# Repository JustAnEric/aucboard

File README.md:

# Aucboard

Revision 2 Aucboard

> [!NOTE]
> This is my first ever hardware project involving CAD/PCB design, if there are any issues you can create one: [Create an issue](https://github.com/JustAnEric/aucboard/issues/new)

Aucboard in its design aims to provide **high fidelity**, 384KHz audio to listeners in a small package.

The hardware I am using/have used to make this project possible:

| Link | Supplier/Seller | Approx. Price |
|------|-----------------|---------------|
| [Common PCM5102A DAC breakout board](https://www.amazon.com.au/VGOL-GY-PCM5102-Compatible-Ardu-inos-Raspberry/dp/B0F631QSCH) | Amazon AU | ~A$20.39 |
| [Raspberry Pi(R) Zero 2 W](https://www.raspberrypi.com/products/raspberry-pi-zero-2-w) | Hack Club (find options near you) | ~US$15.00 |
| [SSD1306 Monochrome OLED display](https://www.amazon.com.au/s?k=ssd1306) | Find options near you | ~A$15.00 - ~A$25.00 |
| Total | | A$69.89 - A$79.89 |

> [!IMPORTANT]
> ***For the perspective of Hack Club's Half Life, I have already bought the Common PCM5102A DAC breakout board, Raspberry Pi(R) Zero 2 W and the SSD1306 Monochrome OLED display myself. PCB manufacturing and fabrication costs are going to be receiving the most funding for this project.***

Tools used:

* KiCAD

The optimal fabrication solution I figured was JLCPCB, as PCBWay can charge $5-10 more per board. If you end up building this yourself, make sure to factor in those costs and whether you'd like PCBA, or manual work. For me, I'll be using PCBA.

## Board revisions

This section will go into the design process of the board.

### Rev 1

The very simplistic schematic of the board is shown below, as it was in V1 (forgetting DAC2, GPIO27, GPIO22, GPIO17, GPIO23 and AGND, I was setting up layouts for an amplifier)

* RPIZ2W1 is the header for the Raspberry Pi Zero 2 W's GPIO connections,
* GPIO5, GPIO6, GPIO13 and GPIO26 are connected to SW1-SW4,
* DISP1 is the SSD1306 OLED display module,
* DAC1 is the 6 pins the DAC provides for outputting a basic line-level signal from its preinstalled AUX jack

And a bit of placement magic onto the PCB, including a ground plane with a 0.2 mm clearance, 0.3 mm thermal relief gap and solid pad connections for some shielding:

(The text and barcode was on the F.Cu layer, I didn't know this at the time and I fixed it to F.Silkscreen instead...)

So afterwards, the PCB would look like this:

<div>

</div>

I tried my best to keep the DIN cable routed at the back and short, I wanted minimal crosstalk between the power and signal lines as is typical practice when making boards like this. Constraints required me to use a lot of vias as you can see via the dots on traces (as shown in KiCAD).

#### Flaws with this current design

This PCB has no real amplification to it. So, the line-level signal coming out from the DAC would actually fail to drive basic headphones properly unfortunately. Another design is needed, and note to self for next time:
* I should fill up as much board space as I can,
* Maybe put the amplifier next to the display,
* Optimize my traces a little more by shortening them and planning out better paths, for the amplifier this is especially important....

### Rev 2

In Revision 2.0, I added an amplifier called the MAX97220AETE+T into the mix and moved some things around. I made the buttons surface-mount so it would be way easier for me to route traces properly across the board. Additionally, there are now less vias, making the board way cleaner. This was done over 10 hours of work approximately, most of me was trying to understand the optimal circuit the PDF datasheet recommended. The amp circuit is effectively the same, but I replaced the input smoothing 0.47uF capacitors with 1uF capacitors to allow a decrease in frequency to ~15Hz rather than ~33Hz minimum.

On the PCB, it received a full re-design, including with how components are placed. Now the DAC is flipped around to the other side and rotated, giving easier access for the amplifier circuit to work properly. There are now two (bigger) ground planes stitched to each other instead of just the one, aiming to provide better thermal spreading, better EMI shielding meaning better signal integrity, and lower impedence ground return paths.

The routing spaghetti is definitely less, automatically allowing for greater reliability because not everything is very packed like Revision 1.

## Software journaling

The software implemented right now at [firmware/](firmware/) is very basic, and definitely needs greater development. Though, the greatest achievement I'm proud of is how `miniaudio` plays audio so smoothly on constrained devices. Furthermore, I can edit the audio stream *in software* rather than constantly configuring a tool like `pactl` filters.

In the first few commits, `pygame` was implemented due to its simpler `pygame.mixer`, but if I kept it like that, audio quality would've been sacrificed heavily for its simplicity. **Heavy stuttering and jitter** would have occurred for the tests directly because of Python (as the same happens with PyAudio too). Miniaudio simplifies it *way* down for Aucboard.

## Disclaimers!

This is an **ongoing project**, and I have not at all started with software yet. This README right now only shows a basic design, where everything may not be up to date as I revise.

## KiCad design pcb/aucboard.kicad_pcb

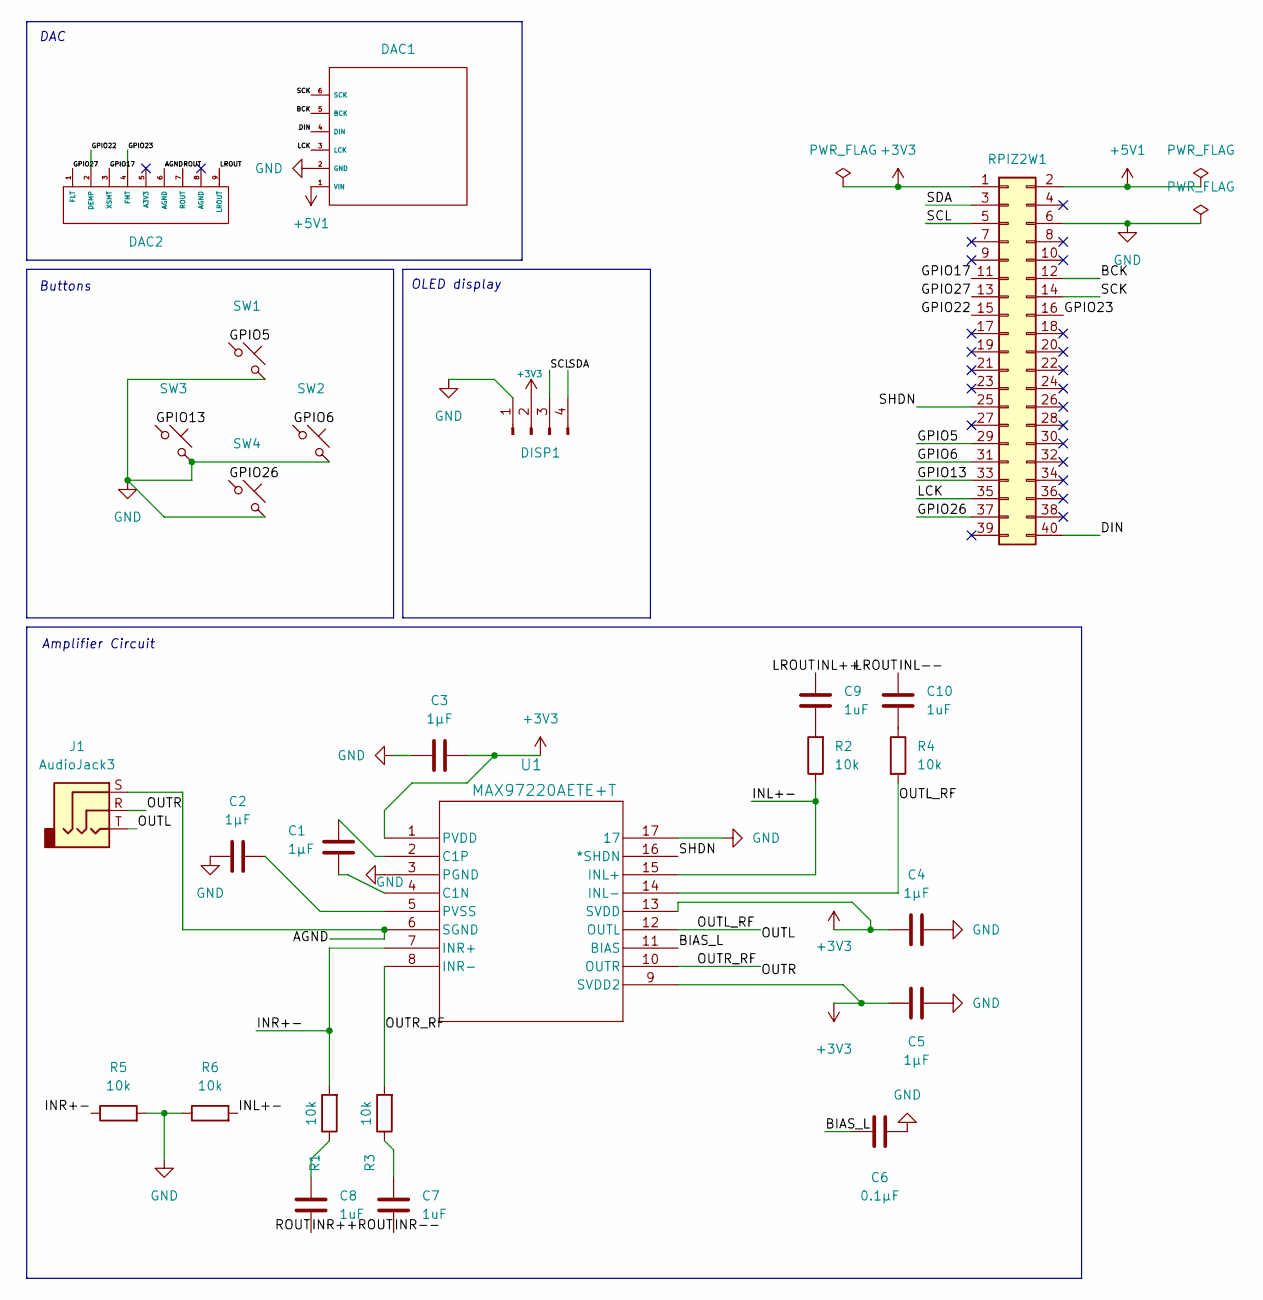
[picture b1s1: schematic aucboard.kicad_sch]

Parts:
C1, C2, C3, C4, C5: 1µF; C_0805_2012Metric_Pad1.18x1.45mm_HandSolder
C6: 0.1µF; C_0805_2012Metric_Pad1.18x1.45mm_HandSolder
C7, C8, C9, C10: 1uF; C_0805_2012Metric_Pad1.18x1.45mm_HandSolder
DAC1: PinSocket_1x06_P2.54mm_Vertical
DAC2: PinSocket_1x09_P2.54mm_Vertical
DISP1: Conn_01x04_Pin; PinSocket_1x04_P2.54mm_Vertical
J1: AudioJack3; Jack_3.5mm_CUI_SJ1-3513N_Horizontal
R1, R2, R3, R4, R5, R6: 10k; R_0805_2012Metric_Pad1.20x1.40mm_HandSolder
RPIZ2W1: Conn_02x20_Odd_Even; PinSocket_2x20_P2.54mm_Vertical
SW1, SW2, SW3, SW4: SW_Push; SW_SPST_PTS645Sx43SMTR92
U1: MAX97220AETE+T; 21-0136I_T1633-4_MXM

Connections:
+3V3: C3.2, C4.1, C5.2, DISP1.2, RPIZ2W1.1, U1.1 (PVDD), U1.9 (SVDD2), U1.13 (SVDD)
+5V1: DAC1.1 (VIN), RPIZ2W1.2
/AGND: DAC2.6 (AGND), J1.S, U1.6 (SGND)
/BCK: DAC1.5 (BCK), RPIZ2W1.12
/BIAS_L: C6.1, U1.11 (BIAS)
/DIN: DAC1.4 (DIN), RPIZ2W1.40
/GPIO5: RPIZ2W1.29, SW1.1
/GPIO6: RPIZ2W1.31, SW2.1
/GPIO13: RPIZ2W1.33, SW3.1
/GPIO17: DAC2.3 (XSMT), RPIZ2W1.11
/GPIO22: DAC2.2 (DEMP), RPIZ2W1.15
/GPIO23: DAC2.4 (FMT), RPIZ2W1.16
/GPIO26: RPIZ2W1.37, SW4.1
/GPIO27: DAC2.1 (FLT), RPIZ2W1.13
/INL++: C9.1, C10.1, DAC2.9 (LROUT)
/INL+-: R2.1, R6.2, U1.15 (INL+)
/INR++: C7.2, C8.2, DAC2.7 (ROUT)
/INR+-: R1.2, R5.1, U1.7 (INR+)
/LCK: DAC1.3 (LCK), RPIZ2W1.35
/OUTL: J1.T, R4.2, U1.12 (OUTL), U1.14 (INL-)
/OUTR: J1.R, R3.2, U1.8 (INR-), U1.10 (OUTR)
/SCK: DAC1.6 (SCK), RPIZ2W1.14
/SCL: DISP1.3, RPIZ2W1.5
/SDA: DISP1.4, RPIZ2W1.3
GND: C2.1, C3.1, C4.2, C5.1, C6.2, DAC1.2 (GND), DISP1.1, R5.2, R6.1, RPIZ2W1.6, SW1.2, SW2.2, SW3.2, SW4.2, U1.3 (PGND), U1.17
unnamed: C7.1, R3.1
unnamed: C8.1, R1.1
unnamed: C9.2, R2.2
unnamed: C10.2, R4.1
unnamed: C1.2, U1.4 (C1N)
unnamed: C1.1, U1.2 (C1P)
unnamed: C2.2, U1.5 (PVSS)

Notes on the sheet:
Amplifier Circuit
DAC
OLED display
Buttons

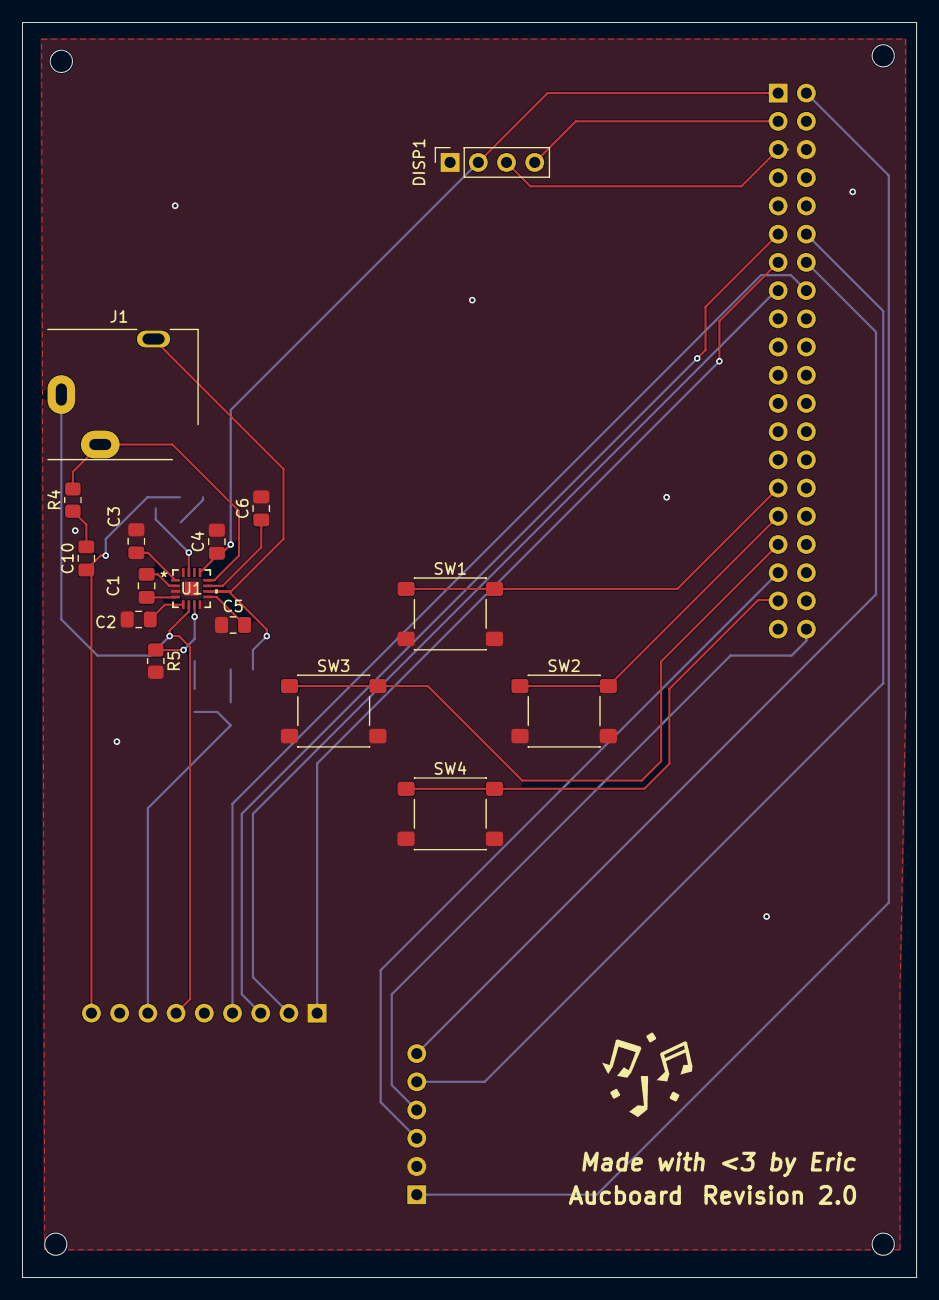
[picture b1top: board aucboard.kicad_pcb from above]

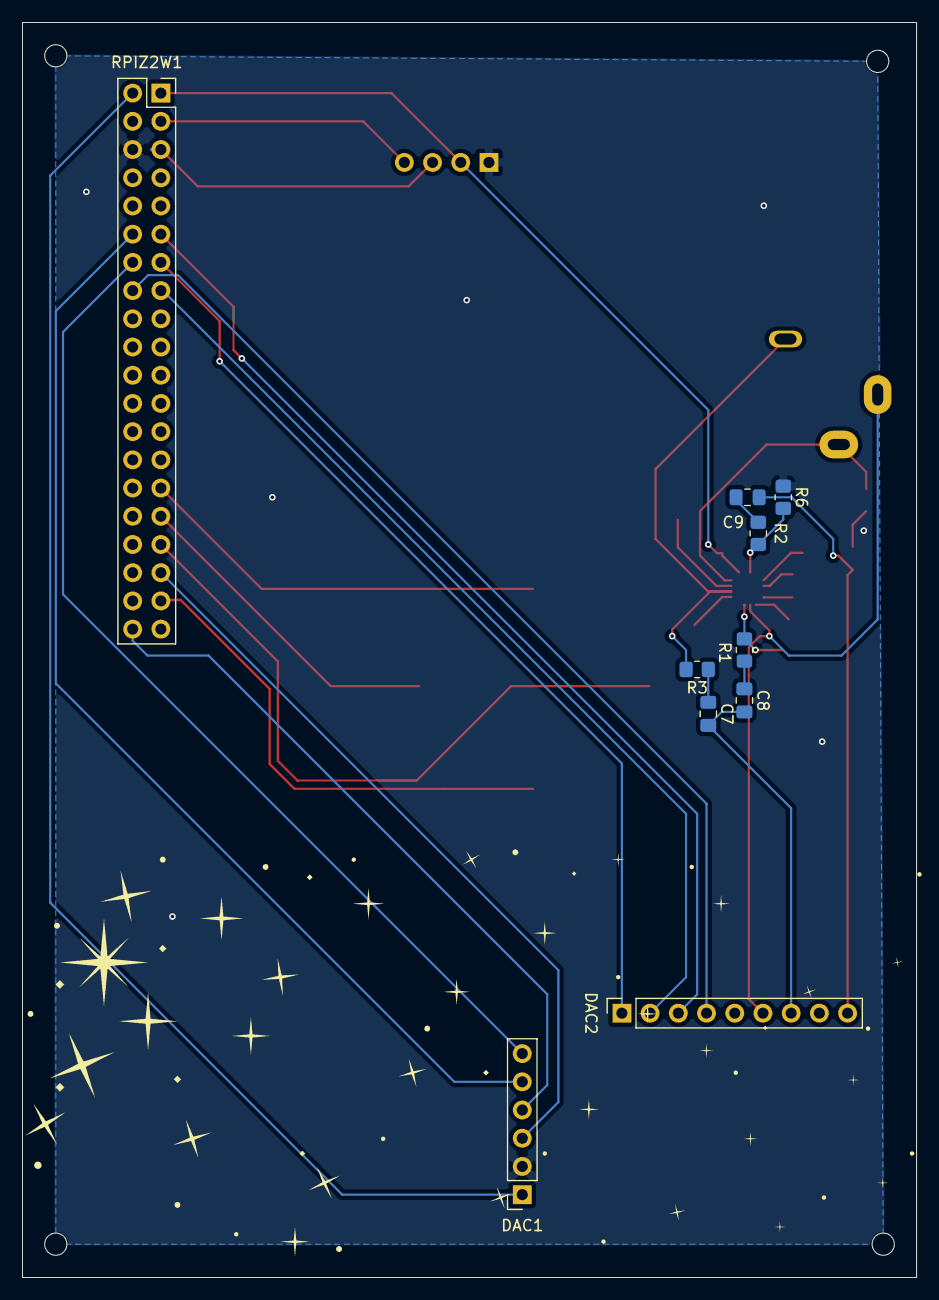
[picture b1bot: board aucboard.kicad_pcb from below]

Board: 2 copper layers, 80.5 x 113.0 mm, 26 parts (10 on the bottom side), 32 nets.
